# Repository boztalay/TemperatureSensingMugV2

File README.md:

TemperatureSensingMugV2
=======================

The second version of a mug that displays the relative temperature of its contents on an LED bargraph

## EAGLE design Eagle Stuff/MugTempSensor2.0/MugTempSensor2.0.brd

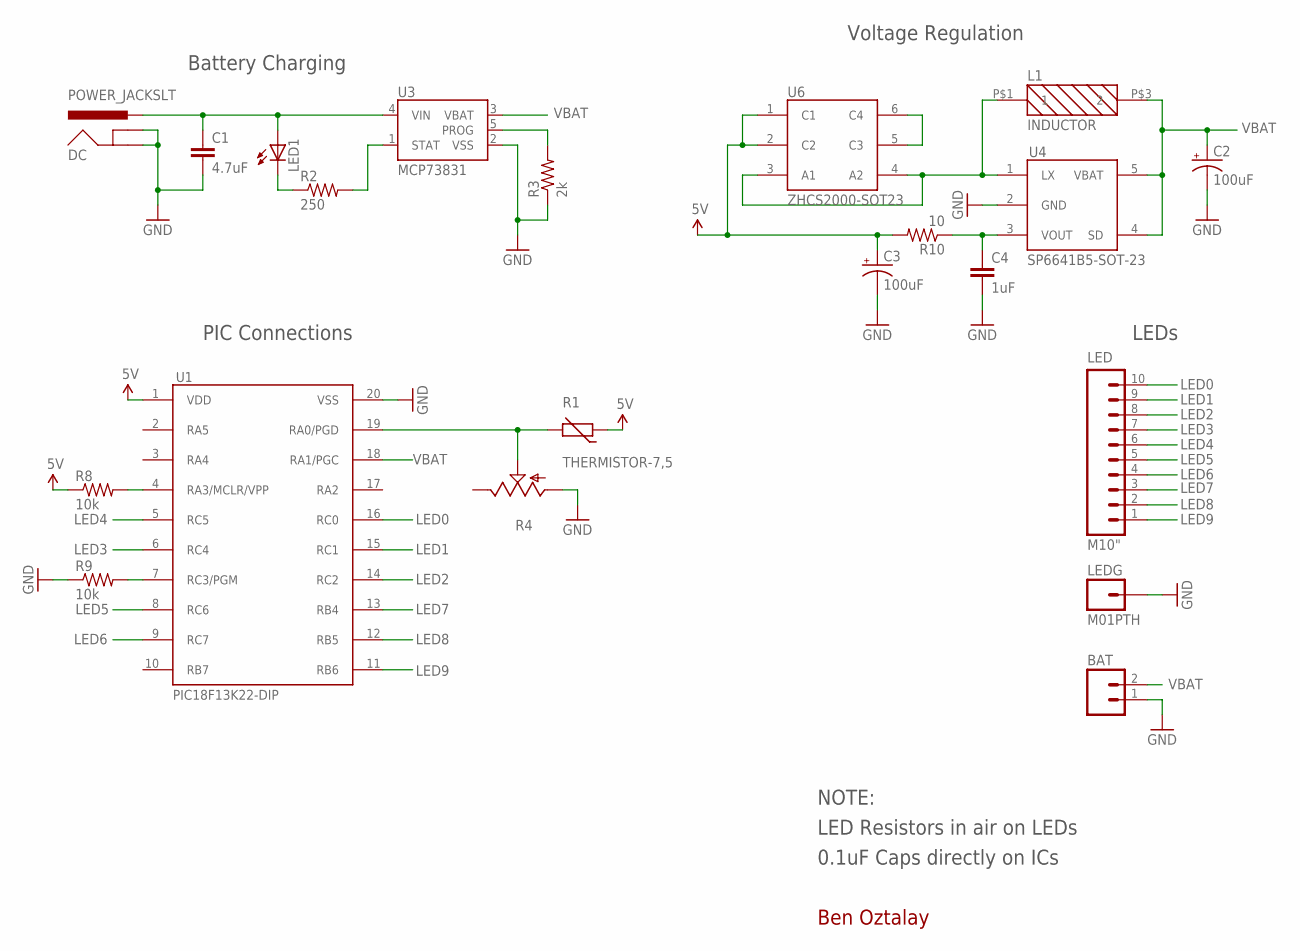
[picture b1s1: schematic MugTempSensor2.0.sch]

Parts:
BAT: M02PTH; 1X02
C1: 4.7uF; CAP-PTH-SMALL
C2, C3: 100uF; EIA7343
C4: 1uF; CAP-PTH-SMALL
DC: POWER_JACKSLT; POWER_JACK_SLOT
L1: INDUCTOR; IND
LED: M10"; 1X10
LED1: LED3MM
LEDG: M01PTH; 1X01
R1: THERMISTOR-7,5; R-7,5
R2: 250; AXIAL-0.3-KIT
R3: 2k; AXIAL-0.3-KIT
R4: TRIM_US-B64Y; B64Y
R8, R9: 10k; AXIAL-0.3-KIT
R10: 10; AXIAL-0.3-KIT
U1: PIC18F13K22-DIP; DIP-20-300MIL
U3: MCP73831; SOT23-5
U4: SP6641B5-SOT-23; SOT-23-5
U6: ZHCS2000-SOT23; SOT-23-6

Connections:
5V: C3.A (+), R1.1, R8.P$1 (1), R10.P$2 (2), U1.1 (VDD), U6.1 (C1), U6.2 (C2)
GND: BAT.1, C1.2, C2.C (-), C3.C (-), C4.2, DC.GND@1 (GNDBREAK), DC.GND@2 (GND), LEDG.1, R3.P$1 (1), R4.A, R9.P$1 (1), U1.20 (VSS), U3.2 (VSS), U4.2 (GND)
LED0: LED.10, U1.16 (RC0)
LED1: LED.9, U1.15 (RC1)
LED2: LED.8, U1.14 (RC2)
LED3: LED.7, U1.6 (RC4)
LED4: LED.6, U1.5 (RC5)
LED5: LED.5, U1.8 (RC6)
LED6: LED.4, U1.9 (RC7)
LED7: LED.3, U1.13 (RB4)
LED8: LED.2, U1.12 (RB5)
LED9: LED.1, U1.11 (RB6)
unnamed: C1.1, DC.PWR, LED1.A, U3.4 (VIN)
unnamed: LED1.K (C), R2.P$1 (1)
unnamed: R2.P$2 (2), U3.1 (STAT)
unnamed: R3.P$2 (2), U3.5 (PROG)
unnamed: R8.P$2 (2), U1.4 (RA3/MCLR/VPP)
unnamed: R9.P$2 (2), U1.7 (RC3/PGM)
unnamed: L1.P$1 (1), U4.1 (LX), U6.3 (A1), U6.4 (A2)
unnamed: U6.5 (C3), U6.6 (C4)
unnamed: C4.1, R10.P$1 (1), U4.3 (VOUT)
unnamed: R1.2, R4.S, U1.19 (RA0/PGD)
VBAT: BAT.2, C2.A (+), L1.P$3 (2), U1.18 (RA1/PGC), U3.3 (VBAT), U4.4 (SD), U4.5 (VBAT)

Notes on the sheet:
Battery Charging
Voltage Regulation
PIC Connections
LEDs
Ben Oztalay
NOTE:
LED Resistors in air on LEDs
0.1uF Caps directly on ICs

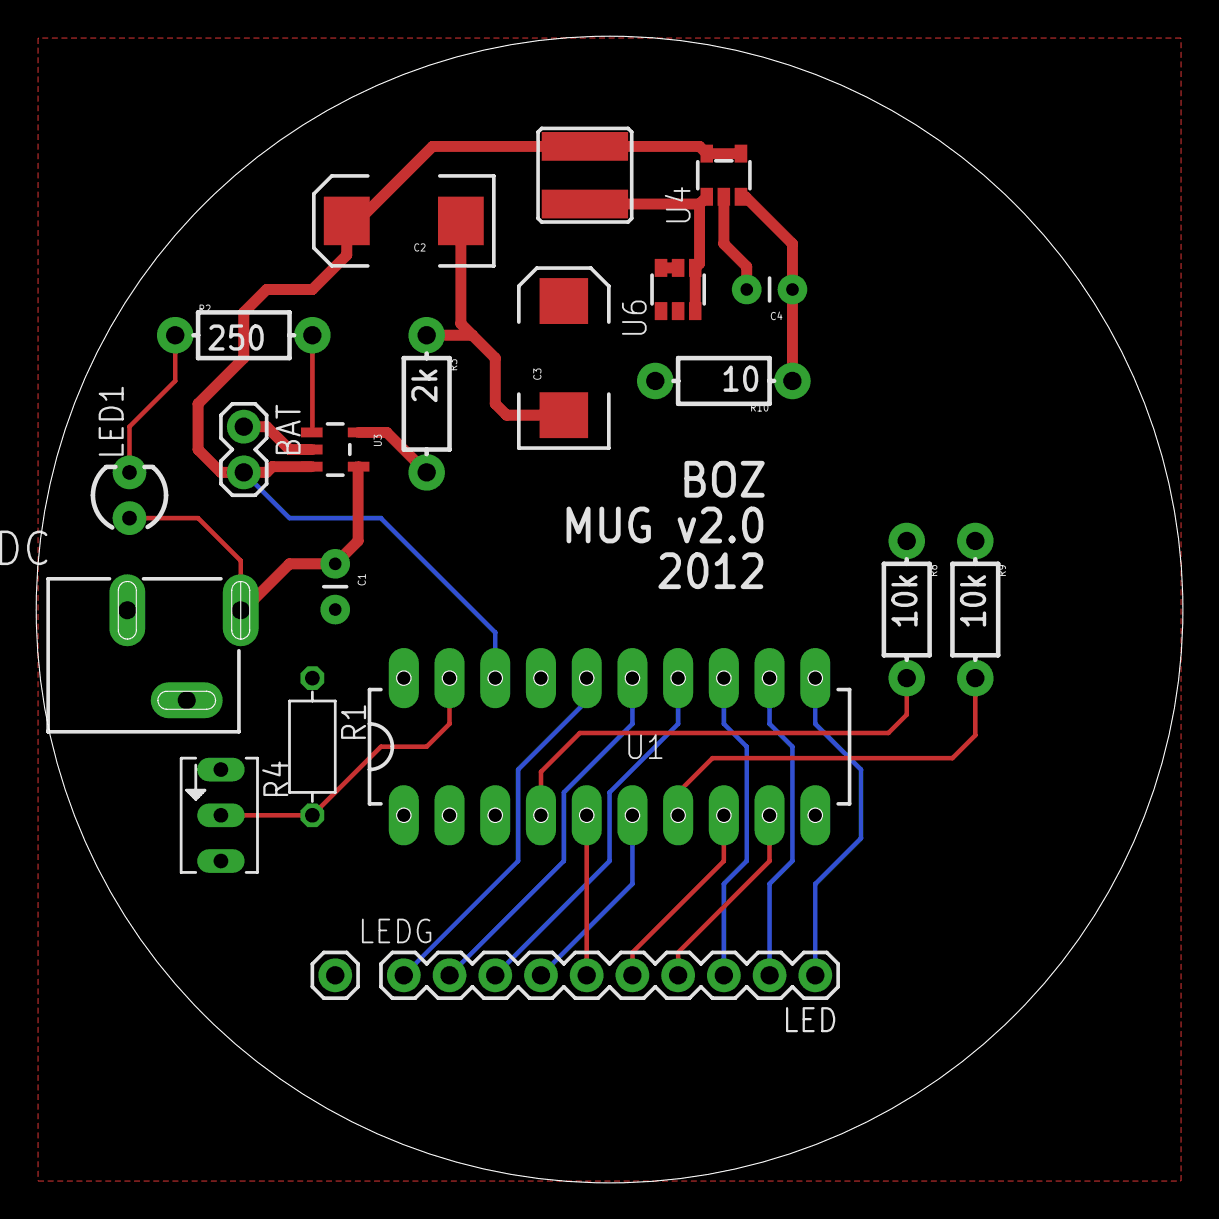
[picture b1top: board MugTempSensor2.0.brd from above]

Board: 2 copper layers, 63.7 x 63.7 mm, 21 parts (0 on the bottom side), 23 nets.

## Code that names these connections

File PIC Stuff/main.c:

#include <p18f13k22.h>

//LED location definitions
#define LED0 LATCbits.LATC0
#define LED1 LATCbits.LATC1
#define LED2 LATCbits.LATC2
#define LED3 LATCbits.LATC4
#define LED4 LATCbits.LATC5
#define LED5 LATCbits.LATC6
#define LED6 LATCbits.LATC7
#define LED7 LATBbits.LATB4
#define LED8 LATBbits.LATB5
#define LED9 LATBbits.LATB6
#define LEDTris1 TRISC
#define LEDTris2 TRISB

//Function prototypes
void ADC_init(void);
void ADC_process(void);
void ADC_switch(unsigned char);

void Comparator_init(void);
void Comparator_process(void);

void Timer_Process(void);

void LED_initPWM(void);
void LED_PWMProcess(void);
void LED_PWMFrameProcess(void); 
void LED_onPWM(char);
void LED_offPWM(char);

void LED_init(void);
void LED_allOff(void);
void LED_allOn(void);
void LED_on(char);
void LED_off(char);

//LED management variables
int brightness[10];
unsigned char status[10];
int currentBrightness;
int frameCount;

//ADC variables
unsigned char ADC_result;
unsigned char ADC_status;
int ADC_val_buffer[13];
int ADC_avg;
char ADC_count;

//Battery Monitoring
unsigned char battery_down;

//Timing out
unsigned char timeOff;

void main() {
	int i = 0;
	int j = 0;

	//Sort out the clock, 64Mhz
	OSCCON = 0b01110000;
	OSCTUNE = 0b11000000;

	LED_init();
	LED_initPWM();
	ADC_init();
	Comparator_init();
	timeOff = 0;

	for(i = 0; i < 10000; i++) {
		for(j = 0; j < 100; j++) {}
	}

	i = 0;

	for(;;) {
		LED_PWMProcess();
		ADC_process();
		Timer_Process();
		Comparator_process();
	
		if(battery_down == 1) {
			LED_allOff();
			Sleep();
			PIE2 = 0b01000000;
			INTCON = 0b01000000;
			PIR2 = 0b00000000;
		} else if(ADC_status == 2) {
			ADC_val_buffer[12] = ADC_val_buffer[11];
			ADC_val_buffer[11] = ADC_val_buffer[10];
			ADC_val_buffer[10] = ADC_val_buffer[9];
			ADC_val_buffer[9] = ADC_val_buffer[8];
			ADC_val_buffer[8] = ADC_val_buffer[7];
			ADC_val_buffer[7] = ADC_val_buffer[6];
			ADC_val_buffer[6] = ADC_val_buffer[5];
			ADC_val_buffer[5] = ADC_val_buffer[4];
			ADC_val_buffer[4] = ADC_val_buffer[3];
			ADC_val_buffer[3] = ADC_val_buffer[2];
			ADC_val_buffer[2] = ADC_val_buffer[1];
			ADC_val_buffer[1] = ADC_val_buffer[0];
			ADC_val_buffer[0] = ADC_result;

			ADC_avg =	ADC_val_buffer[12] + ADC_val_buffer[11] +
						ADC_val_buffer[10] + ADC_val_buffer[9] + ADC_val_buffer[8] + 
						ADC_val_buffer[7] +	ADC_val_buffer[6] + ADC_val_buffer[5] +
						ADC_val_buffer[4] + ADC_val_buffer[3] + ADC_val_buffer[2] +
						ADC_val_buffer[1] +	ADC_val_buffer[0];
			ADC_avg = ADC_avg / 13;

			Timer_Process();
			
			if(timeOff == 0) {				
				for(i = 0; ADC_avg > 132; i++) {
					ADC_avg = ADC_avg - 11;
					LED_onPWM(i);
	 			}
				for(i; i < 10; i++) {
					LED_offPWM(i);
				}
			} else {
				LED_allOff();
			}

			ADC_status = 0;
		}
	}
}

//OTHER FUNCTIONS

void ADC_init() {
	//Set up RA0 as an analog input,
	//all that other fun stuff
	int i = 0;

	ANSELbits.ANS0 = 1;
	TRISAbits.TRISA0 = 1;
	ADCON1 = 0b00000000;
	ADCON2 = 0b00010111;
	ADCON0 = 0b00000001;

	ADC_result = 0;
	ADC_status = 0; //No operation in progress

	for(i = 0; i < 13; i++) {
		ADC_val_buffer[i] = 0;
	}

	ADC_avg = 0;
	ADC_count = 0;
}

void ADC_process() {
	//If there isn't an operation in progress...
	if(ADC_status == 0) {
		ADC_count++;
		if(ADC_count == 5) {
			//Start an operation
			ADCON0bits.GO = 1;
			ADC_status = 1;
			ADC_count = 0;
		}
	} else if(ADC_status == 1) {
		//If the operation is over, take care of bidniz
		if(ADCON0bits.GO == 0) {
			ADC_status = 2;
			ADC_result = ADRESH;
		}
	}
}

void Comparator_init() {
	TRISAbits.TRISA1 = 1;

	//Set up VREF
	VREFCON0 = 0b10110000;
	VREFCON1 = 0b11001000;
	VREFCON2 = 0b00011100;

	//Set up the comparator
	CM1CON0 = 0b10010100;

	//Set up interrupts
	PIE2 = 0b01000000;
	INTCON = 0b01000000;

	battery_down = 0;
}

void Comparator_process() {
	int i = 0;
	if(battery_down == 0) {
		if((CM1CON0 & 0b01000000) == 0b00000000) {
			battery_down = 1;
			VREFCON0 = 0b00110000;
			VREFCON1 = 0b01001000;
			CM1CON0 = 0b00010100;

			for(i = 0; i < 100; i++) {}

			VREFCON0 = 0b10110000;
			VREFCON1 = 0b11001000;
			VREFCON2 = 0b00011111; //has to go back above 31
			CM1CON0 = 0b10010100;
		}
	} else {
		if((CM1CON0 & 0b01000000) == 0b01000000) {
			battery_down = 0;
			VREFCON0 = 0b00110000;
			VREFCON1 = 0b01001000;
			CM1CON0 = 0b00010100;

			for(i = 0; i < 100; i++) {}

			VREFCON0 = 0b10110000;
			VREFCON1 = 0b11001000;
			VREFCON2 = 0b00011100; //has to go back below 28
			CM1CON0 = 0b10010100;
		}
	}
}

void Timer_Process() {
	if(ADC_result < ADC_val_buffer[2]) {
		if(ADC_avg < 145) {
			if(frameCount > 1000) {
				timeOff = 1;
			}
		}	
	} else {
		if(ADC_avg > 175) {
			timeOff = 0;
			frameCount = 0;
		}
	}
}

void LED_initPWM() {
	int i = 0;
	currentBrightness = 0;
	frameCount = 0;

	for(i = 0; i < 10; i++) {
		brightness[i] = 0;
		status[i] = 0;
	}
}

void LED_PWMProcess() {
	int i = 0;

	if(timeOff == 1) {
		return;
	}

	for(i = 0; i < 10; i++) {
		if((brightness[i] >= currentBrightness) && (brightness[i] != 0)) {
			LED_on(i);
		} else {
			LED_off(i);
		}
	}

	currentBrightness = currentBrightness + 1;
	if(currentBrightness == 255) {
		currentBrightness = 0;
		frameCount++;
		LED_PWMFrameProcess();
	}

	return;
}

void LED_PWMFrameProcess() {
	int i = 0;

	for(i = 0; i < 10; i++) {
		switch(status[i]) {
			case 0: //dead
				LED_off(i);
				break;
			case 1: //alive
				LED_on(i);
				break;
			case 2: //dying
				if(brightness[i] == 0) {
					status[i] = 0;
				}
				brightness[i]--;
				break;
			case 3: //born
				if(brightness[i] == 255) {
					status[i] = 1;
				}
				brightness[i]++;
				break;
			default: break;
		}
	}
}

void LED_onPWM(char ledNum) {
	if(status[ledNum] != 1) {
		status[ledNum] = 3;
	}
}

void LED_offPWM(char ledNum) {
	if(status[ledNum] != 0) {
		status[ledNum] = 2;
	}
}

void LED_allOff() {
	LED0 = 0;
	LED1 = 0;
	LED2 = 0;
	LED3 = 0;
	LED4 = 0;
	LED5 = 0;
	LED6 = 0;
	LED7 = 0;
	LED8 = 0;
	LED9 = 0;
}

void LED_allOn() {
	LED0 = 1;
	LED1 = 1;
	LED2 = 1;
	LED3 = 1;
	LED4 = 1;
	LED5 = 1;
	LED6 = 1;
	LED7 = 1;
	LED8 = 1;
	LED9 = 1;
}

void LED_on(char ledNum) {
	switch(ledNum) {
		case 0: LED0 = 1; break;
		case 1: LED1 = 1; break;
		case 2: LED2 = 1; break;
		case 3: LED3 = 1; break;
		case 4: LED4 = 1; break;
		case 5: LED5 = 1; break;
		case 6: LED6 = 1; break;
		case 7: LED7 = 1; break;
		case 8: LED8 = 1; break;
		case 9: LED9 = 1; break;
		default: break;
	}
}

void LED_off(char ledNum) {
	switch(ledNum) {
		case 0: LED0 = 0; break;
		case 1: LED1 = 0; break;
		case 2: LED2 = 0; break;
		case 3: LED3 = 0; break;
		case 4: LED4 = 0; break;
		case 5: LED5 = 0; break;
		case 6: LED6 = 0; break;
		case 7: LED7 = 0; break;
		case 8: LED8 = 0; break;
		case 9: LED9 = 0; break;
		default: break;
	}
}

void LED_init() {
	LEDTris1 = 0x00;
	LEDTris2 = 0x00;

	LED_allOff();
}

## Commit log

2013-09-27 Update LICENSE
2013-09-28 Adding all files
